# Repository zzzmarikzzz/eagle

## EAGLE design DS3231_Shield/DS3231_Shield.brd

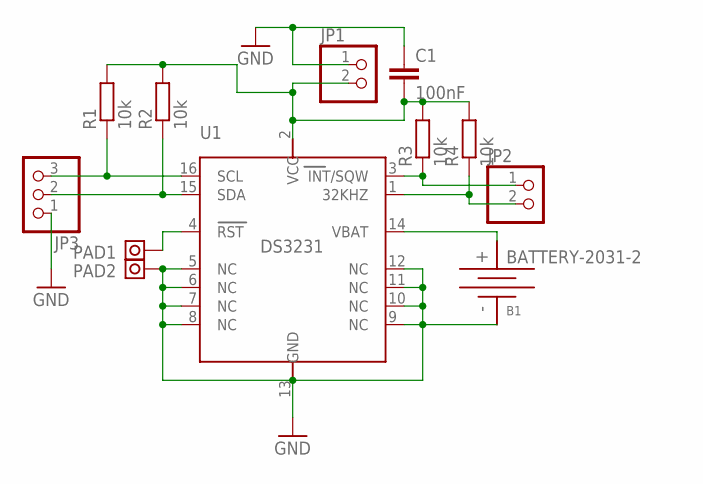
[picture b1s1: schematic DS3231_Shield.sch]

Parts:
B1: BATTERY-2031-2; BTH2032-2
C1: 100nF; C0805
JP1, JP2: PINHD-1X2; 1X02
JP3: PINHD-1X3; 1X03
PAD1, PAD2: PAD
R1, R2, R3, R4: 10k; R0805
U1: DS3231; SO16L

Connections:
GND: B1.-, C1.1, JP1.1, JP3.1, PAD2.P$1, U1.5 (NC), U1.6 (NC), U1.7 (NC), U1.8 (NC), U1.9 (NC), U1.10 (NC), U1.11 (NC), U1.12 (NC), U1.13 (GND)
unnamed: C1.2, JP1.2, R1.2, R2.2, R3.2, R4.2, U1.2 (VCC)
unnamed: B1.+, U1.14 (VBAT)
unnamed: PAD1.P$1, U1.4 (RST)
unnamed: JP3.2, R2.1, U1.15 (SDA)
unnamed: JP3.3, R1.1, U1.16 (SCL)
unnamed: JP2.1, R3.1, U1.3 (INT/SQW)
unnamed: JP2.2, R4.1, U1.1 (32KHZ)

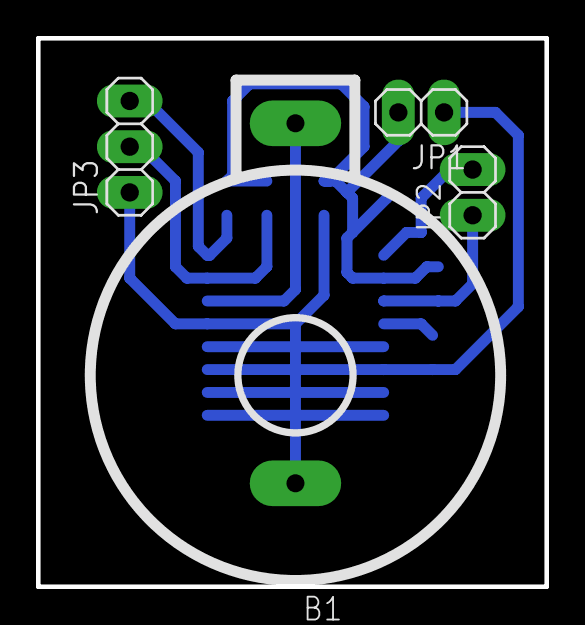
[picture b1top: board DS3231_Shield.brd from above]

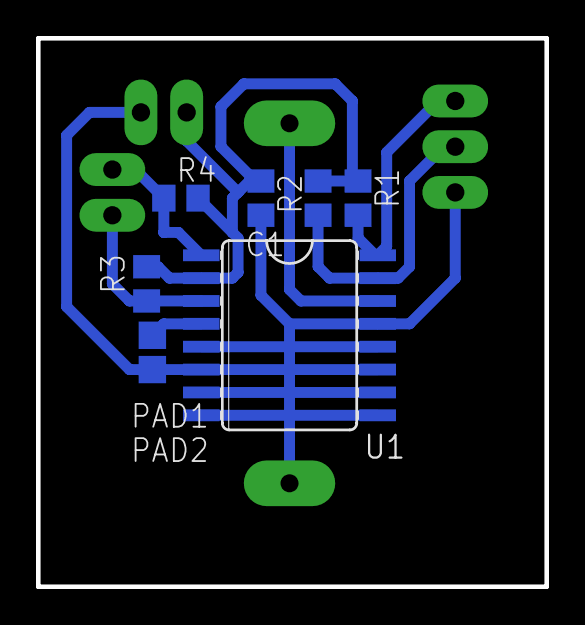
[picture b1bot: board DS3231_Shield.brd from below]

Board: 2 copper layers, 28.2 x 30.5 mm, 12 parts (8 on the bottom side), 8 nets.

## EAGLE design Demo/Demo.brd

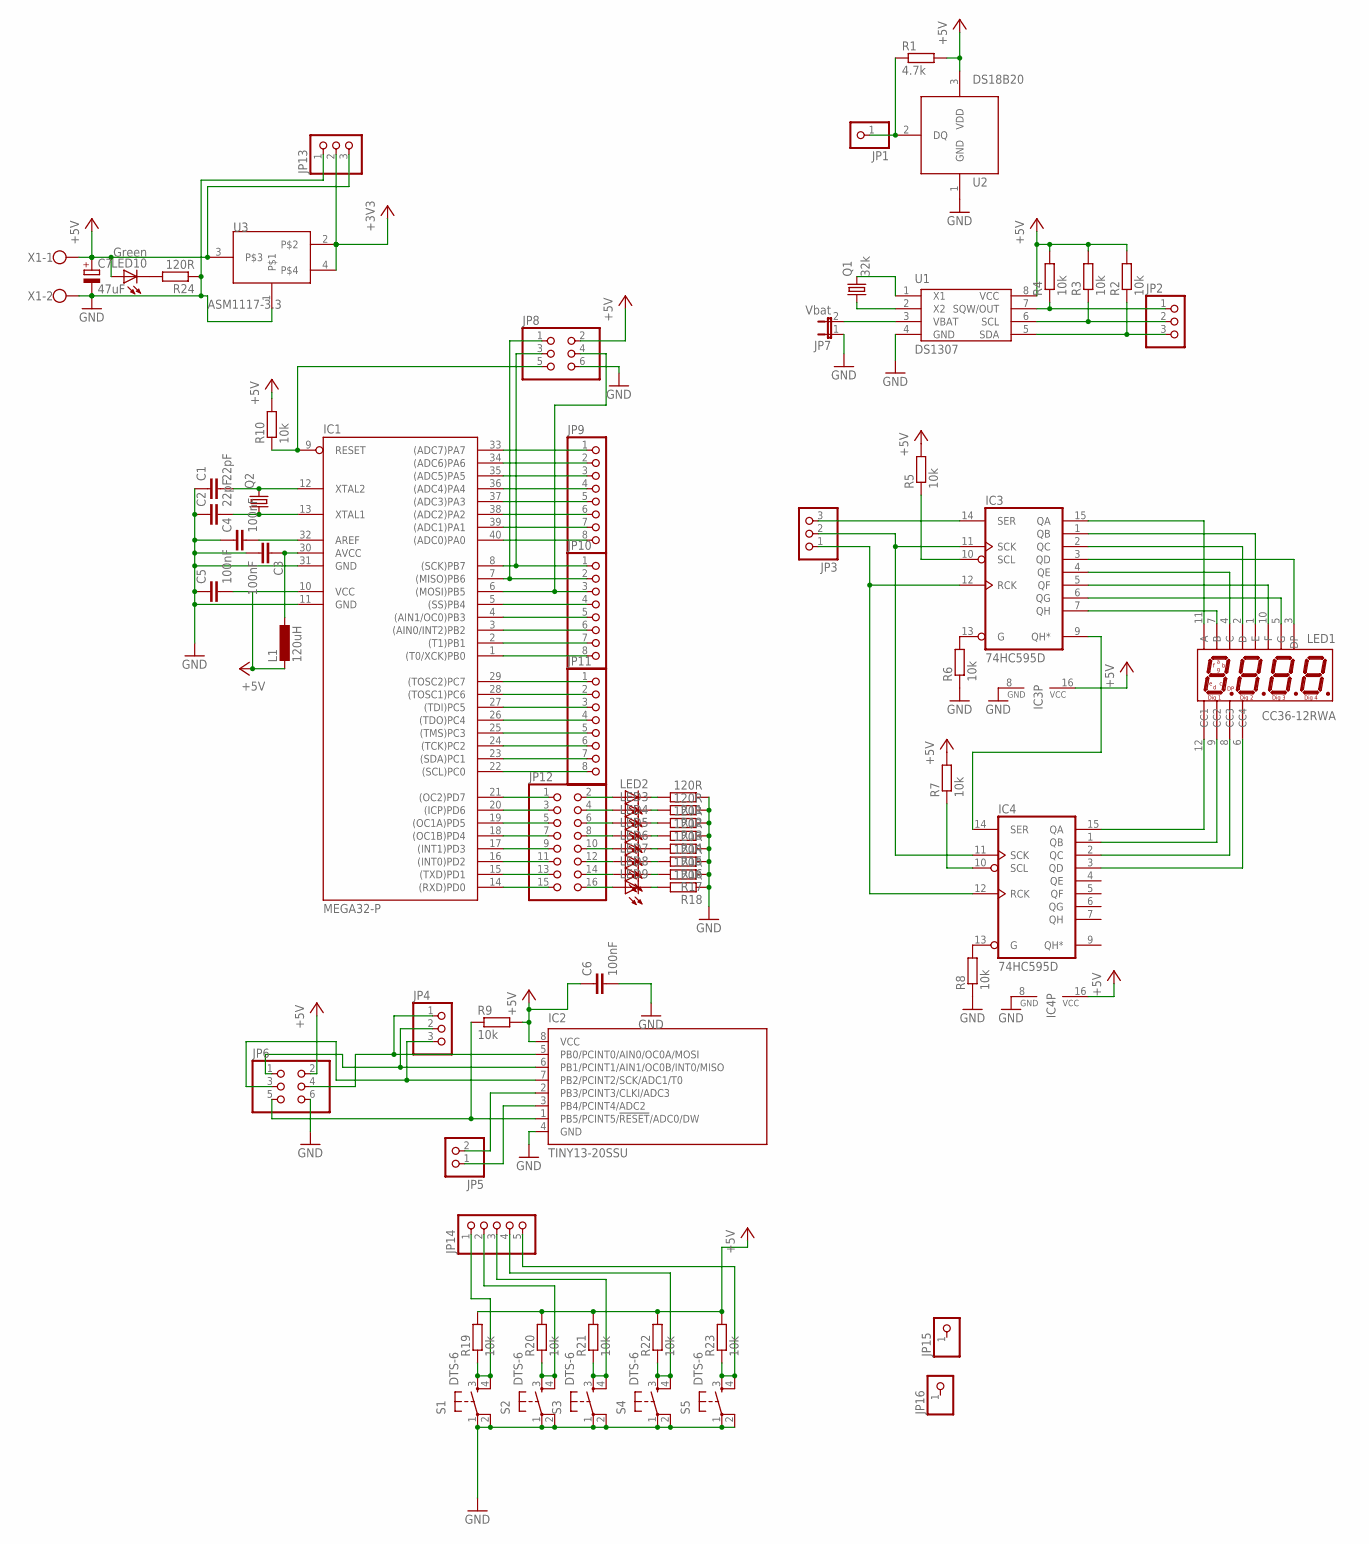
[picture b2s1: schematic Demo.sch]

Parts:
C1, C2: 22pF; C0805
C3, C4, C5, C6: 100nF; C0805
C7: 47uF; E2-5
IC1: MEGA32-P; DIL40
IC2: TINY13-20SSU; 8S1
IC3, IC4: 74HC595D; SO16
JP1, JP15, JP16: PINHD-1X1; 1X01
JP2, JP3, JP4, JP13: PINHD-1X3; 1X03
JP5: PINHD-1X2; 1X02
JP6, JP8: PINHD-2X3; 2X03
JP7: Vbat; JP1
JP9, JP10, JP11: PINHD-1X8; 1X08
JP12: PINHD-2X8; 2X08
JP14: PINHD-1X5; 1X05
L1: 120uH; 0204V
LED1: CC36-12RWA; 7SEG_4DIG
LED2, LED3, LED4, LED5, LED6, LED7, LED8, LED9: LEDSML0603; SML0603
LED10: Green; SML0603
Q1: 32k; TC38H
Q2: CRYSTALHC49S; HC49/S
R1: 4.7k; R0603
R2, R3, R4, R5, R6, R7, R8, R9, R10, R19, R20, R21, R22, R23: 10k; R0603
R11, R12, R13, R14, R15, R16, R17, R18, R24: 120R; R0603
S1, S2, S3, S4, S5: DTS-6
U1: DS1307; SOP08
U2: DS18B20; TO92
U3: ASM1117-3.3; SOT223
X1: W237-102

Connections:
+3V3: JP13.2, U3.2, U3.4
+5V: C5.2, C6.1, C7.+, IC1.10 (VCC), IC2.8 (VCC), IC3.16 (VCC), IC4.16 (VCC), JP6.2, JP8.2, JP13.3, L1.2, LED10.A, R1.2, R2.2, R3.2, R4.2, R5.2, R7.2, R9.2, R10.2, R19.2, R20.2, R21.2, R22.2, R23.2, U1.8 (VCC), U2.3 (VDD), U3.3, X1.1
GND: C1.1, C2.1, C3.2, C4.1, C5.1, C6.2, C7.-, IC1.11 (GND), IC1.31 (GND), IC2.4 (GND), IC3.8 (GND), IC4.8 (GND), JP6.6, JP7.1, JP8.6, JP13.1, R6.1, R8.1, R11.1, R12.1, R13.1, R14.1, R15.1, R16.1, R17.1, R18.1, R24.1, S1.1, S1.2, S2.1, S2.2, S3.1, S3.2, S4.1, S4.2, S5.1, S5.2, U1.4 (GND), U2.1 (GND), U3.1, X1.2
unnamed: JP1.1, R1.1, U2.2 (DQ)
unnamed: Q1.1, U1.2 (X2)
unnamed: Q1.2, U1.1 (X1)
unnamed: JP7.2, U1.3 (VBAT)
unnamed: JP2.3, R2.1, U1.5 (SDA)
unnamed: JP2.2, R3.1, U1.6 (SCL)
unnamed: JP2.1, R4.1, U1.7 (SQW/OUT)
unnamed: IC3.10 (SCL), R5.1
unnamed: IC3.13 (G), R6.2
unnamed: IC4.13 (G), R8.2
unnamed: IC4.10 (SCL), R7.1
unnamed: IC3.9 (QH*), IC4.14 (SER)
unnamed: IC3.15 (QA), LED1.11 (A)
unnamed: IC3.1 (QB), LED1.1 (E)
unnamed: IC3.2 (QC), LED1.2 (D)
unnamed: IC3.3 (QD), LED1.3 (DP)
unnamed: IC3.4 (QE), LED1.4 (C)
unnamed: IC3.5 (QF), LED1.10 (F)
unnamed: IC3.6 (QG), LED1.5 (G)
unnamed: IC3.7 (QH), LED1.7 (B)
unnamed: IC4.15 (QA), LED1.12 (CC1)
unnamed: IC4.1 (QB), LED1.9 (CC2)
unnamed: IC4.2 (QC), LED1.8 (CC3)
unnamed: IC4.3 (QD), LED1.6 (CC4)
unnamed: IC3.14 (SER), JP3.3
unnamed: IC3.11 (SCK), IC4.11 (SCK), JP3.2
unnamed: IC3.12 (RCK), IC4.12 (RCK), JP3.1
unnamed: IC2.1 (PB5/PCINT5/!RESET!/ADC0/DW), JP6.5, R9.1
unnamed: C1.2, IC1.12 (XTAL2), Q2.2
unnamed: IC2.6 (PB1/PCINT1/AIN1/OC0B/INT0/MISO), JP4.2, JP6.1
unnamed: IC2.7 (PB2/PCINT2/SCK/ADC1/T0), JP4.3, JP6.3
unnamed: IC2.5 (PB0/PCINT0/AIN0/OC0A/MOSI), JP4.1, JP6.4
unnamed: IC2.3 (PB4/PCINT4/ADC2), JP5.1
unnamed: IC2.2 (PB3/PCINT3/CLKI/ADC3), JP5.2
unnamed: C2.2, IC1.13 (XTAL1), Q2.1
unnamed: C4.2, IC1.32 (AREF)
unnamed: LED10.C, R24.2
unnamed: C3.1, IC1.30 (AVCC), L1.1
unnamed: IC1.9 (RESET), JP8.5, R10.1
unnamed: IC1.33 ((ADC7)PA7), JP9.1
unnamed: IC1.34 ((ADC6)PA6), JP9.2
unnamed: IC1.35 ((ADC5)PA5), JP9.3
unnamed: IC1.36 ((ADC4)PA4), JP9.4
unnamed: IC1.37 ((ADC3)PA3), JP9.5
unnamed: IC1.38 ((ADC2)PA2), JP9.6
unnamed: IC1.39 ((ADC1)PA1), JP9.7
unnamed: IC1.40 ((ADC0)PA0), JP9.8
unnamed: IC1.8 ((SCK)PB7), JP8.3, JP10.1
unnamed: IC1.7 ((MISO)PB6), JP8.1, JP10.2
unnamed: IC1.6 ((MOSI)PB5), JP8.4, JP10.3
unnamed: IC1.5 ((SS)PB4), JP10.4
unnamed: IC1.4 ((AIN1/OC0)PB3), JP10.5
unnamed: IC1.3 ((AIN0/INT2)PB2), JP10.6
unnamed: IC1.2 ((T1)PB1), JP10.7
unnamed: IC1.1 ((T0/XCK)PB0), JP10.8
unnamed: IC1.29 ((TOSC2)PC7), JP11.1
unnamed: IC1.28 ((TOSC1)PC6), JP11.2
unnamed: IC1.27 ((TDI)PC5), JP11.3
unnamed: IC1.26 ((TDO)PC4), JP11.4
unnamed: IC1.25 ((TMS)PC3), JP11.5
unnamed: IC1.24 ((TCK)PC2), JP11.6
unnamed: IC1.23 ((SDA)PC1), JP11.7
unnamed: IC1.22 ((SCL)PC0), JP11.8
unnamed: IC1.21 ((OC2)PD7), JP12.1
unnamed: IC1.20 ((ICP)PD6), JP12.3
unnamed: IC1.19 ((OC1A)PD5), JP12.5
unnamed: IC1.18 ((OC1B)PD4), JP12.7
unnamed: IC1.17 ((INT1)PD3), JP12.9
unnamed: IC1.16 ((INT0)PD2), JP12.11
unnamed: IC1.15 ((TXD)PD1), JP12.13
unnamed: IC1.14 ((RXD)PD0), JP12.15
unnamed: JP12.2, LED2.A
unnamed: JP12.4, LED3.A
unnamed: JP12.6, LED4.A
unnamed: JP12.8, LED5.A
unnamed: JP12.10, LED6.A
unnamed: JP12.12, LED7.A
unnamed: JP12.14, LED8.A
unnamed: JP12.16, LED9.A
unnamed: LED2.C, R11.2
unnamed: LED3.C, R12.2
unnamed: LED4.C, R13.2
unnamed: LED5.C, R14.2
unnamed: LED6.C, R15.2
unnamed: LED7.C, R16.2
unnamed: LED8.C, R17.2
unnamed: LED9.C, R18.2
unnamed: JP14.1, R19.1, S1.3, S1.4
unnamed: JP14.2, R20.1, S2.3, S2.4
unnamed: JP14.3, R21.1, S3.3, S3.4
unnamed: JP14.4, R22.1, S4.3, S4.4
unnamed: JP14.5, R23.1, S5.3, S5.4

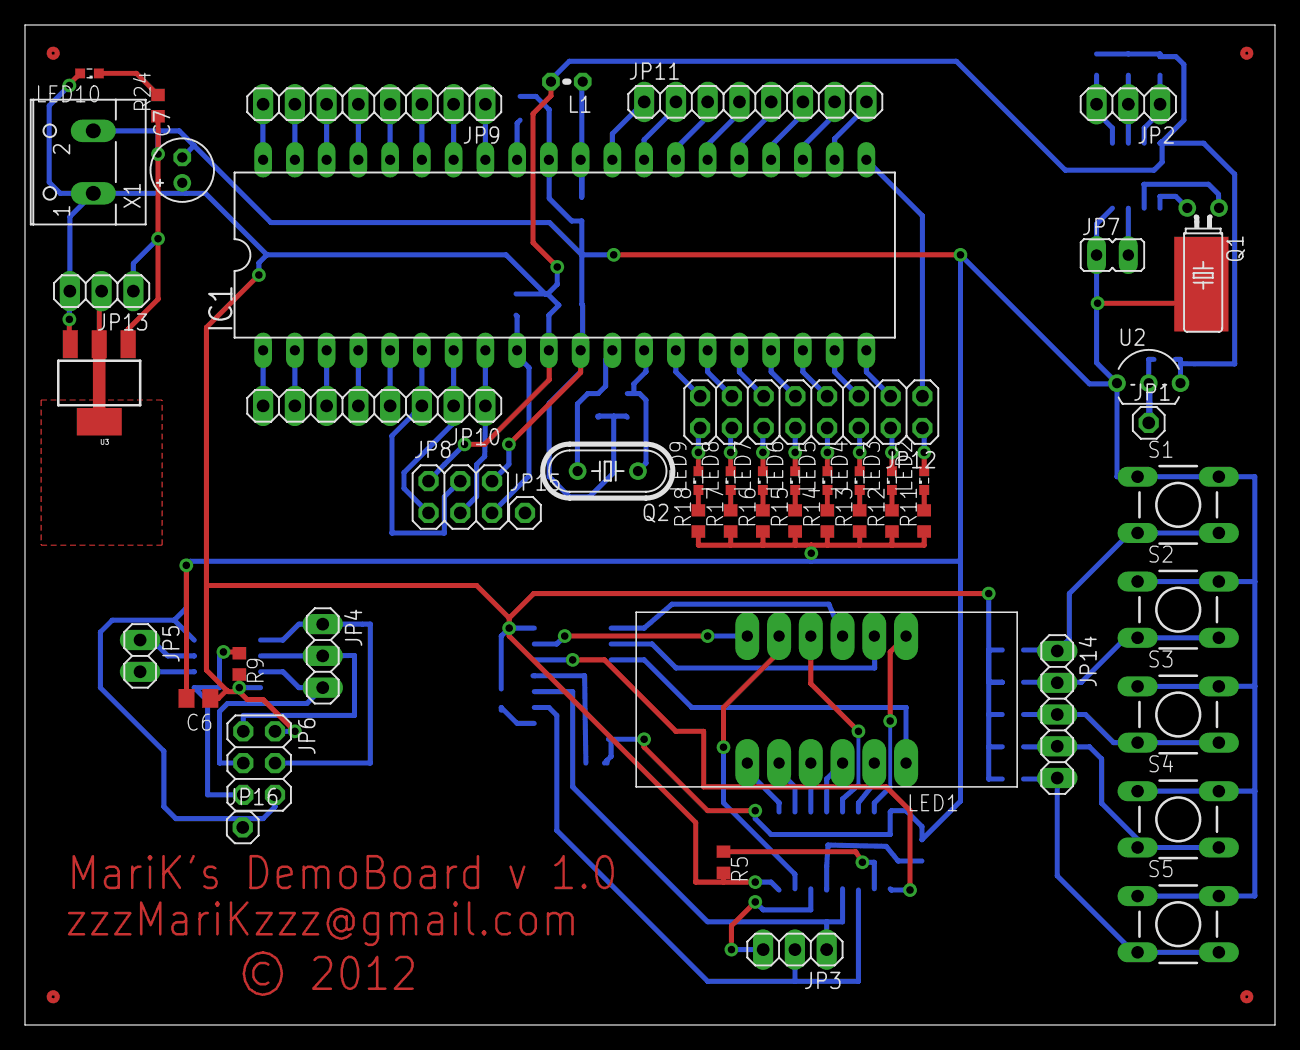
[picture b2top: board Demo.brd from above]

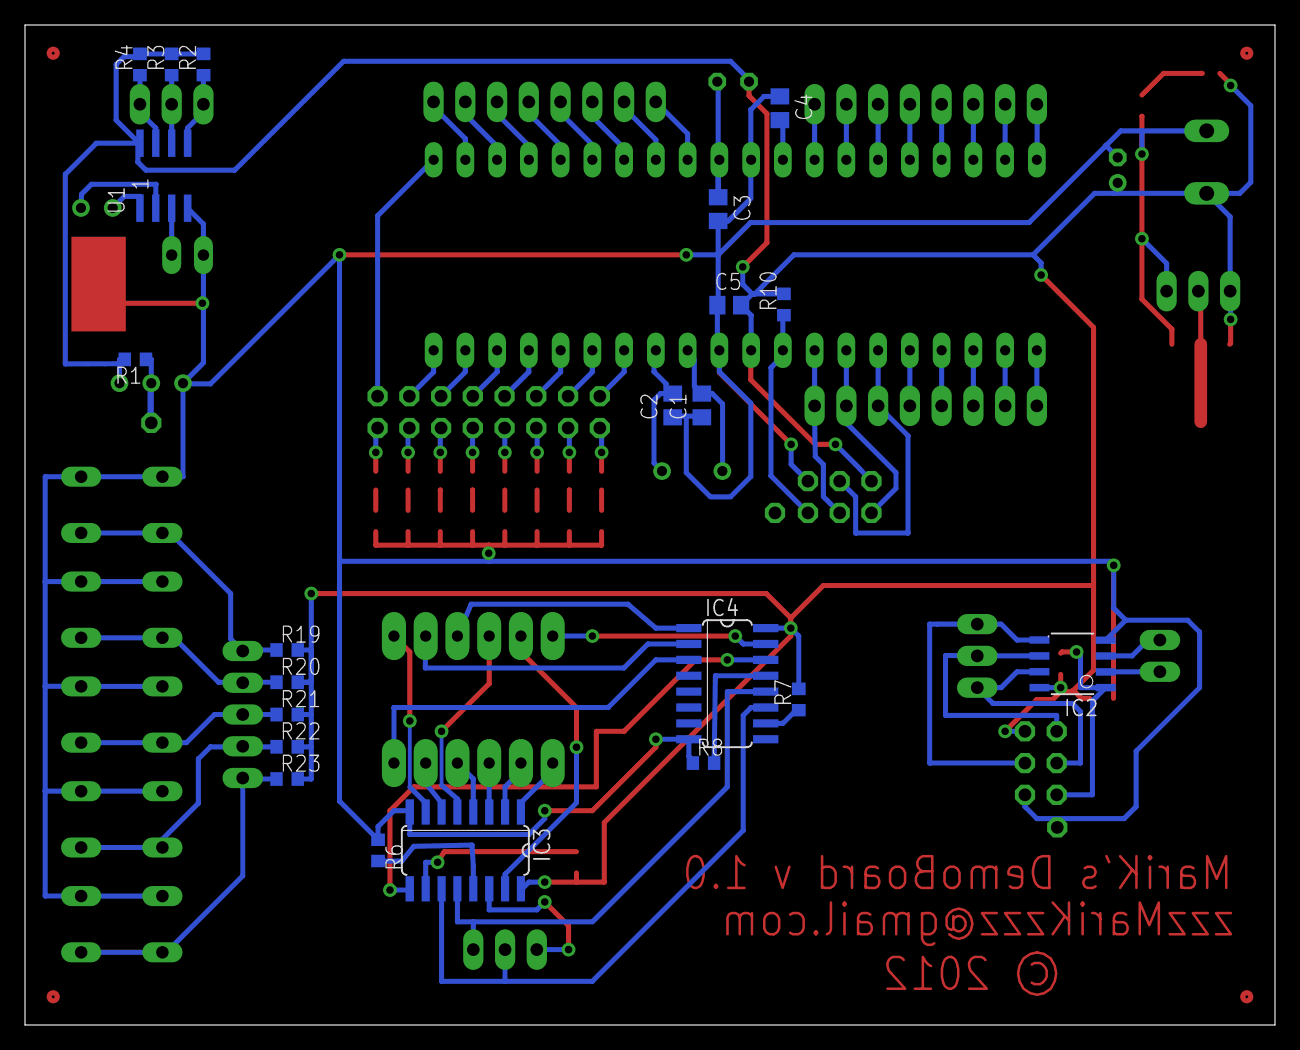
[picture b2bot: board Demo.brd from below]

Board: 2 copper layers, 100.0 x 80.0 mm, 73 parts (22 on the bottom side), 95 nets.

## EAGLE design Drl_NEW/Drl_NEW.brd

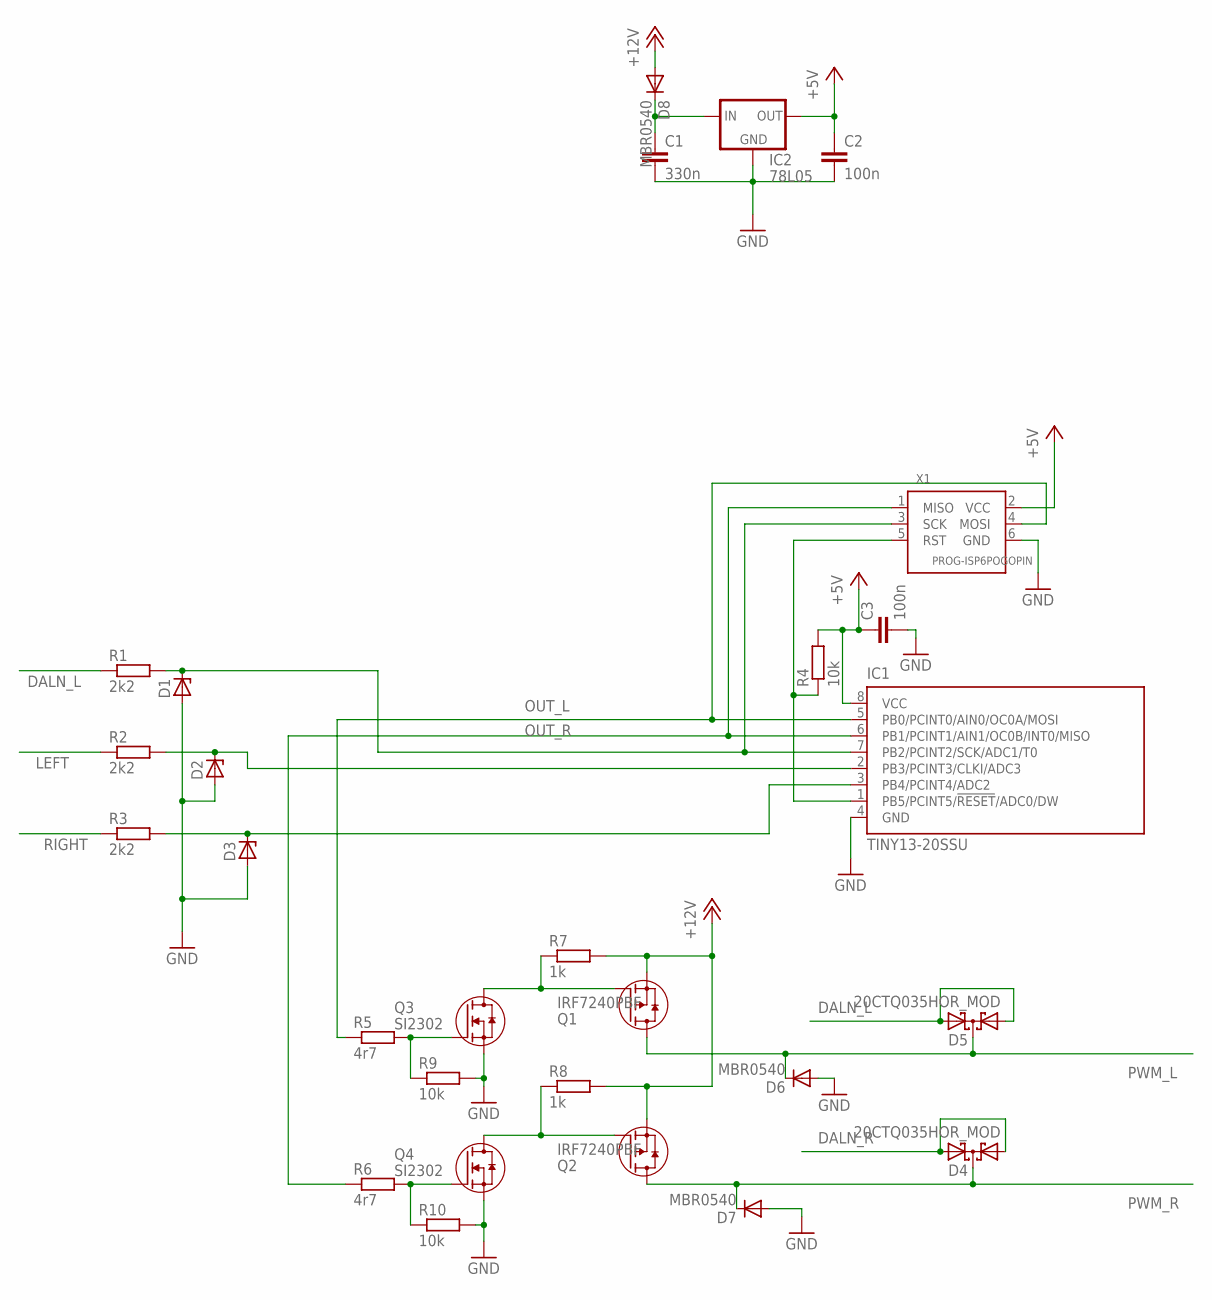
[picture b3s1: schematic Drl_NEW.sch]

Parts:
C1: 330n; C0805
C2, C3: 100n; C0805
D1, D2, D3: ZENER-DIODESOD80C; SOD80C
D4, D5: 20CTQ035HOR_MOD; TO220AB_MOD
D6, D7, D8: MBR0540; SOD-123_MINI-SMA
IC1: TINY13-20SSU; 8S1
IC2: 78L05; 78LXX-SOT89
Q1, Q2: IRF7240PBF; SO08
Q3, Q4: SI2302; SOT-23-GSD
R1, R2, R3: 2k2; R0603
R4, R9, R10: 10k; R0603
R5, R6: 4r7; R0603
R7, R8: 1k; R0603
X1: PROG-ISP6POGOPIN; PROG_POGOPIN

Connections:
+5V: C2.1, C3.1, IC1.8 (VCC), IC2.OUT, R4.2, X1.2 (VCC)
+12V: D8.A, Q1.1 (S), Q1.2 (S), Q1.3 (S), Q2.1 (S), Q2.2 (S), Q2.3 (S), R7.2, R8.2
DALN_L: D5.A1, D5.A2, R1.1
DALN_R: D4.A1, D4.A2
GND: C1.2, C2.2, C3.2, D1.A, D2.A, D3.A, D6.A, D7.A, IC1.4 (GND), IC2.GND@0 (GND), IC2.GND@1 (GND), Q3.S, Q4.S, R9.2, R10.2, X1.6 (GND)
LEFT: R2.1
unnamed: D2.C, IC1.2 (PB3/PCINT3/CLKI/ADC3), R2.2
unnamed: IC1.1 (PB5/PCINT5/!RESET!/ADC0/DW), R4.1, X1.5 (RST)
unnamed: Q2.4 (G), Q4.D, R8.1
unnamed: C1.1, D8.C, IC2.IN
unnamed: D3.C, IC1.3 (PB4/PCINT4/ADC2), R3.2
unnamed: Q1.4 (G), Q3.D, R7.1
unnamed: Q3.G, R5.2, R9.1
unnamed: Q4.G, R6.2, R10.1
unnamed: D1.C, IC1.7 (PB2/PCINT2/SCK/ADC1/T0), R1.2, X1.3 (SCK)
OUT_L: IC1.5 (PB0/PCINT0/AIN0/OC0A/MOSI), R5.1, X1.4 (MOSI)
OUT_R: IC1.6 (PB1/PCINT1/AIN1/OC0B/INT0/MISO), R6.1, X1.1 (MISO)
PWM_L: D5.C, D6.C, Q1.5 (D), Q1.6 (D), Q1.7 (D), Q1.8 (D)
PWM_R: D4.C, D7.C, Q2.5 (D), Q2.6 (D), Q2.7 (D), Q2.8 (D)
RIGHT: R3.1

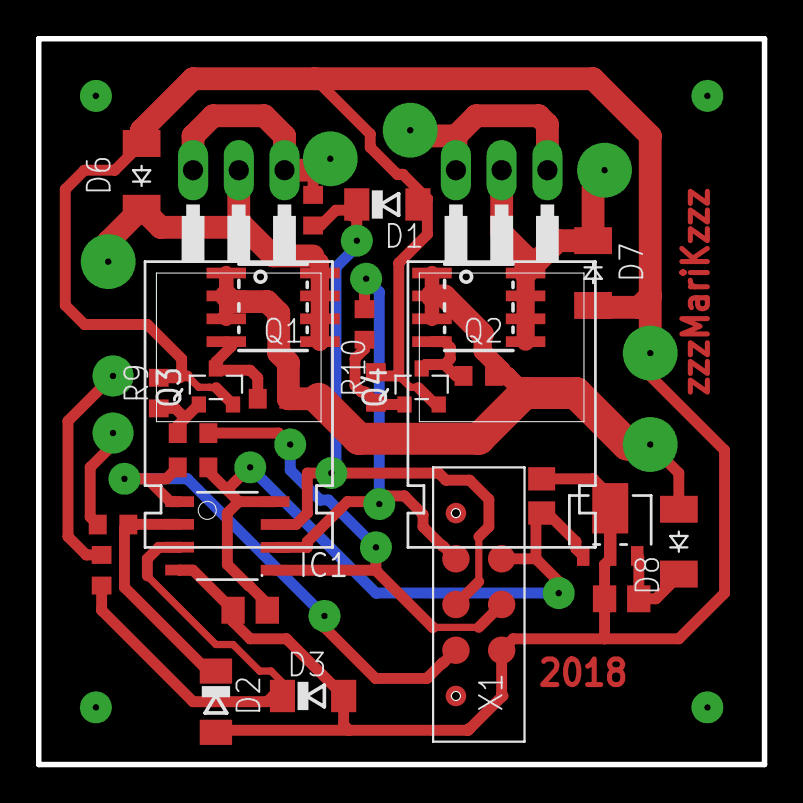
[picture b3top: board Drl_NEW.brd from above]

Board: 2 copper layers, 40.3 x 40.3 mm, 28 parts (0 on the bottom side), 18 nets.

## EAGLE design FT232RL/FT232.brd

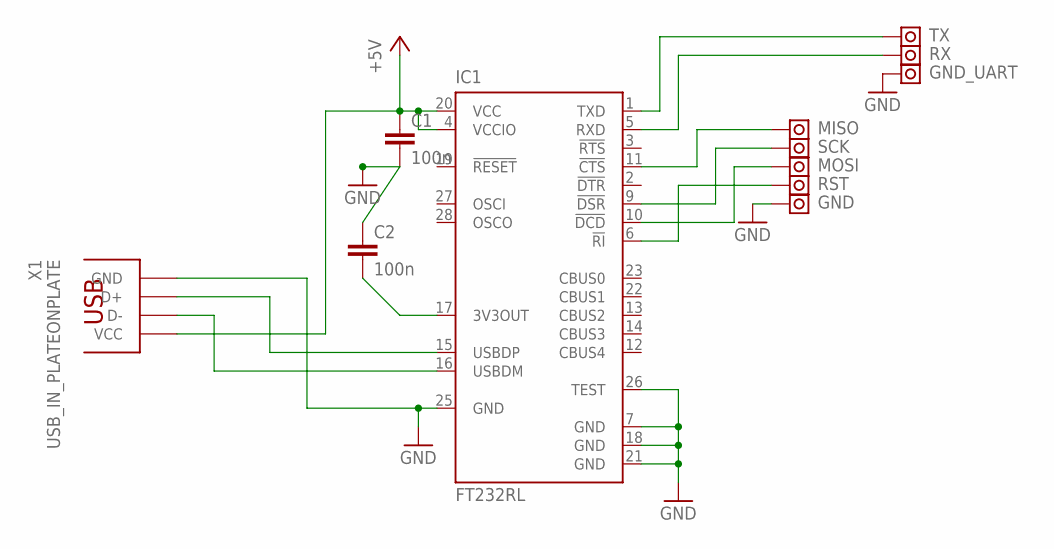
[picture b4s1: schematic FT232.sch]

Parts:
C1: 100n; C0805
C2: 100n; 0805
GND: PAD
GND_UART: PAD
IC1: FT232RL; SSOP28
MISO: PAD
MOSI: PAD
RST: PAD
RX: PAD
SCK: PAD
TX: PAD
X1: USB_IN_PLATEONPLATE; USB_IN_PLATE

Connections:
+5V: C1.1, IC1.4 (VCCIO), IC1.20 (VCC), X1.VCC
GND: C1.2, C2.1, GND.P$1, GND_UART.P$1, IC1.7 (GND), IC1.18 (GND), IC1.21 (GND), IC1.25 (GND), IC1.26 (TEST), X1.GND
unnamed: IC1.1 (TXD), TX.P$1
unnamed: IC1.15 (USBDP), X1.D+
unnamed: IC1.16 (USBDM), X1.D-
unnamed: C2.2, IC1.17 (3V3OUT)
unnamed: IC1.5 (RXD), RX.P$1
unnamed: IC1.11 (!CTS), MISO.P$1
unnamed: IC1.9 (!DSR), SCK.P$1
unnamed: IC1.10 (!DCD), MOSI.P$1
unnamed: IC1.6 (!RI), RST.P$1

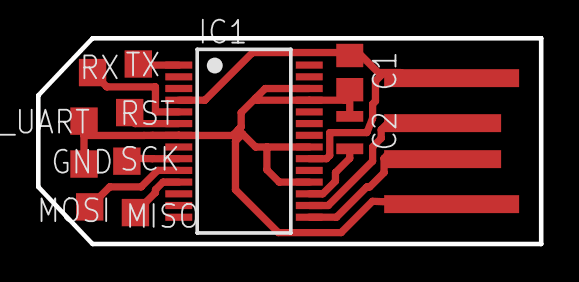
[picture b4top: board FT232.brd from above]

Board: 2 copper layers, 27.9 x 11.4 mm, 12 parts (0 on the bottom side), 11 nets.

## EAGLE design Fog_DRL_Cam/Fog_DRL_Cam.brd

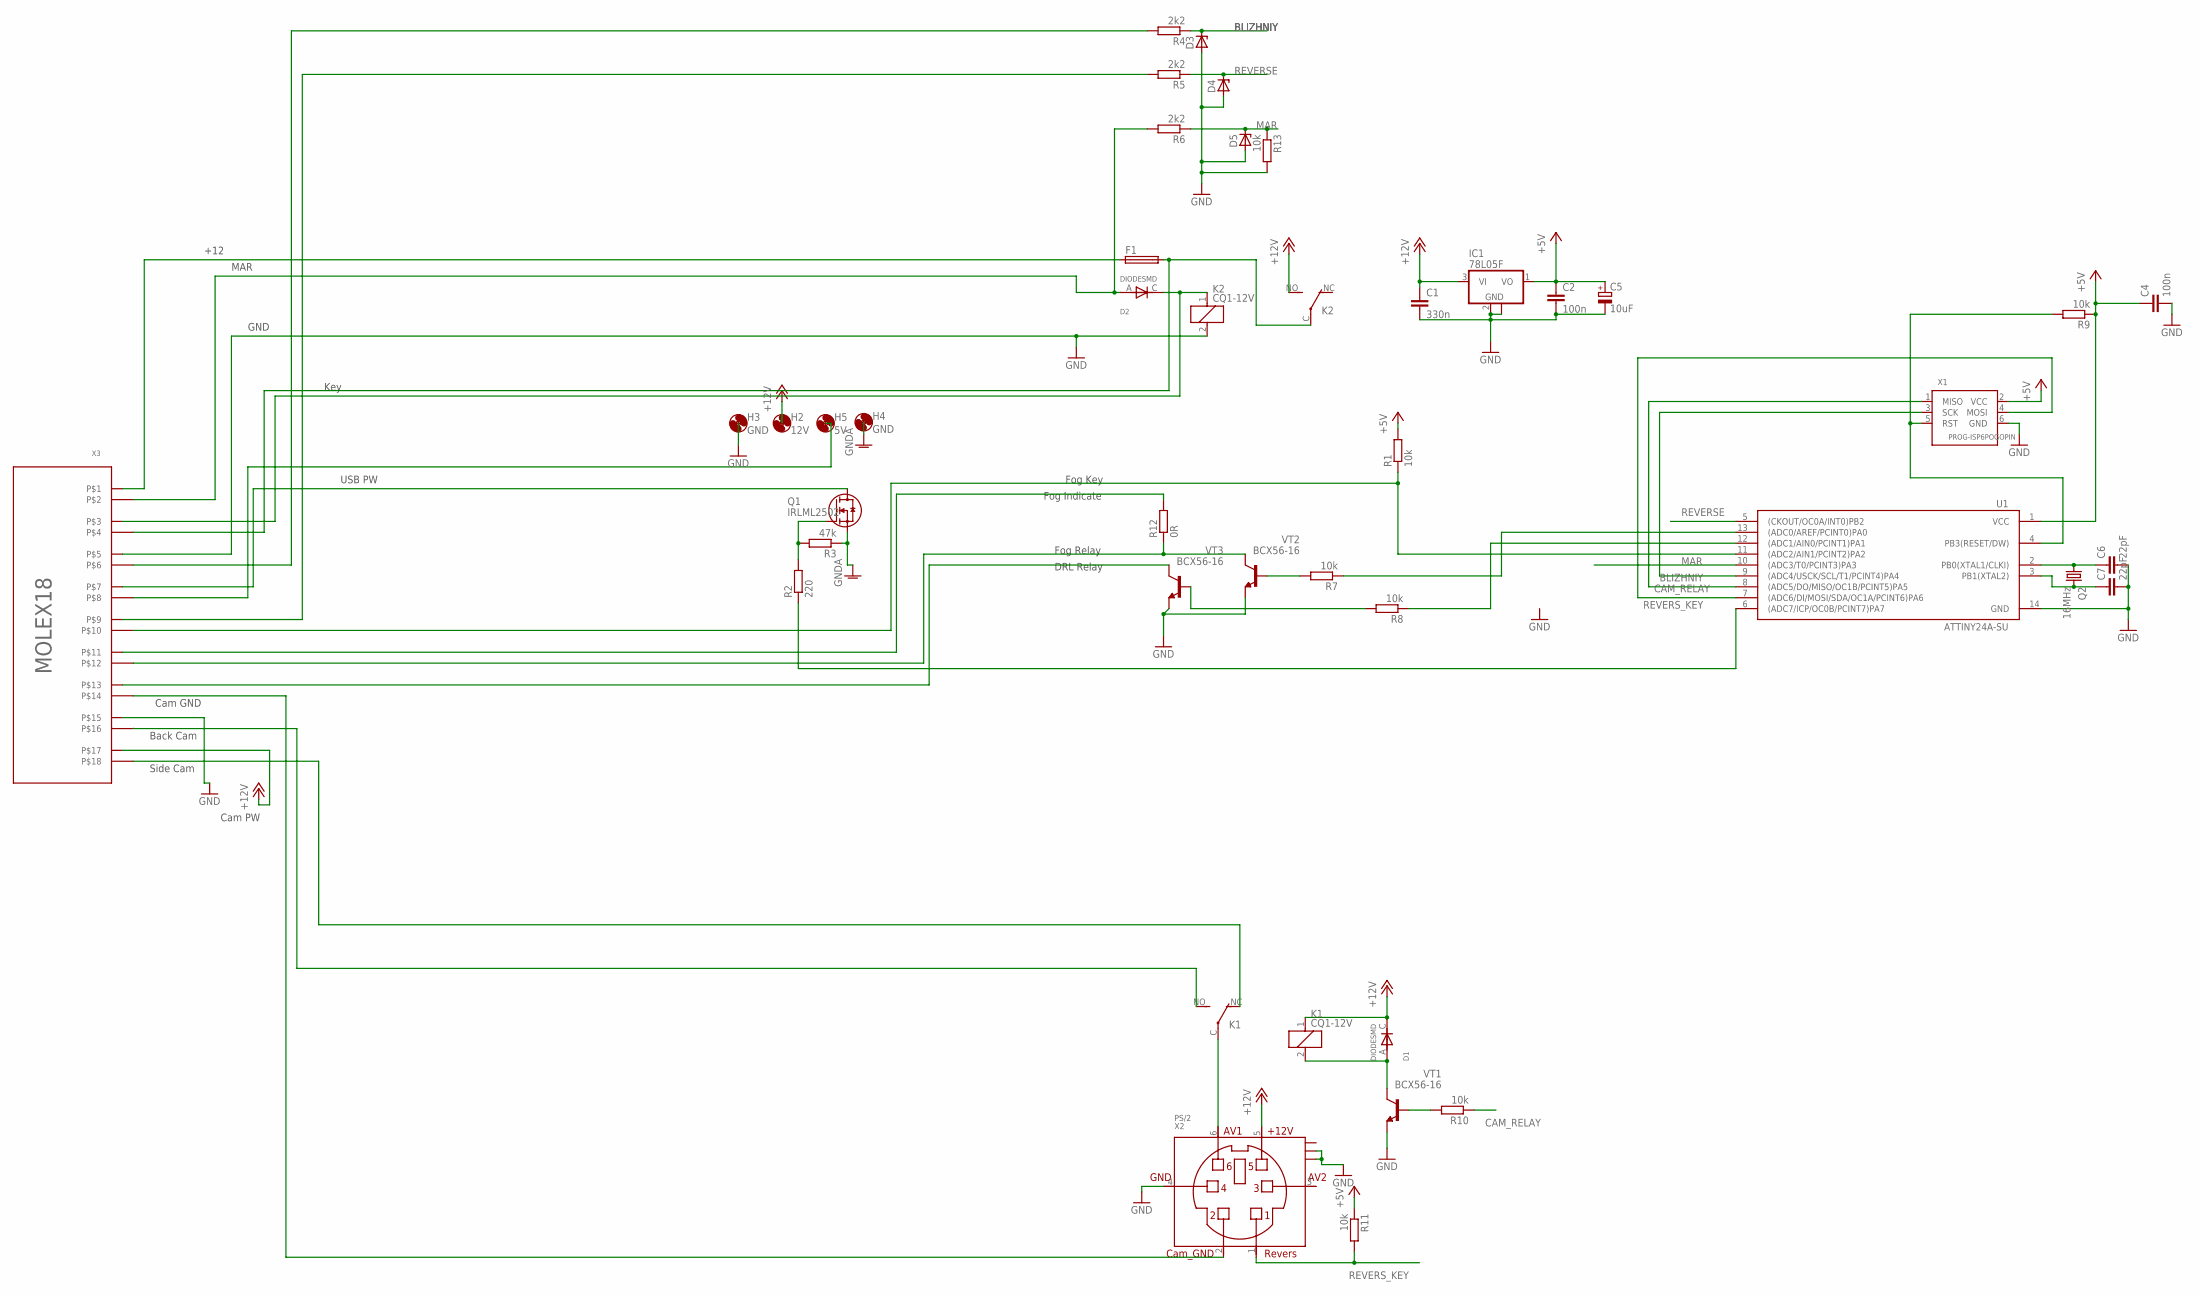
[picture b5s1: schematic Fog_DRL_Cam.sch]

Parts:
C1: 330n; C0805
C2, C4: 100n; C0603
C5: 10uF; CT3216
C6, C7: 22pF; C0603
D1, D2: DIODESMD; DO214AC
D3, D4, D5: ZENER-DIODESOD80C; SOD80C
F1: SH22,5A
H2: 12V; 3,0
H3, H4: GND; 3,0
H5: 5V; 3,0
IC1: 78L05F; SOT89
K1, K2: CQ1-12V; CQ1
Q1: IRLML2502; SOT-23-GSD
Q2: 16MHz; HC49/S
R1, R7, R8, R9, R10, R11, R13: 10k; R0603
R2: 220; R0603
R3: 47k; R0603
R4, R5, R6: 2k2; R0603
R12: 0R; R0603
U1: ATTINY24A-SU; SO14
VT1, VT2, VT3: BCX56-16; SOT89-BCE
X1: PROG-ISP6POGOPIN; PROG_POGOPIN
X2: PS/2
X3: MOLEX18

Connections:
+5V: C2.1, C4.1, C5.+, IC1.1 (VO), R1.2, R9.1, R11.1, U1.1 (VCC), X1.2 (VCC)
+12V: C1.1, D1.C (KATOD), H2.P$1, IC1.3 (VI), K1.1, K2.NO (S), X2.5, X3.P$17
BLIZHNIY: D3.C, R4.1, U1.9 ((ADC4/USCK/SCL/T1/PCINT4)PA4), X1.3 (SCK)
CAM_RELAY: R10.1, U1.8 ((ADC5/DO/MISO/OC1B/PCINT5)PA5), X1.1 (MISO)
GND: C1.2, C2.2, C4.2, C5.-, C6.2, C7.2, D3.A, D4.A, D5.A, H3.P$1, IC1.2 (GND), IC1.2@1 (GND), K2.2, R13.2, U1.14 (GND), VT1.E, VT2.E, VT3.E, X1.6 (GND), X2.4, X2.GND0, X2.GND2, X3.P$5, X3.P$15
GNDA: H4.P$1, Q1.S, R3.1
MAR: D5.C, R6.1, R13.1, U1.10 ((ADC3/T0/PCINT3)PA3)
unnamed: K1.NO (S), X3.P$16
unnamed: R12.2, X3.P$11
unnamed: X2.2, X3.P$14
unnamed: K1.C, X2.6
unnamed: D1.A (ANOD), K1.2, VT1.C, VT1.C@1 (C)
unnamed: F1.1, X3.P$1
unnamed: H5.P$1, X3.P$8
unnamed: Q1.D, X3.P$7
unnamed: F1.2, K2.C, X3.P$4
unnamed: D2.C (KATOD), K2.1, X3.P$3
unnamed: D2.A (ANOD), R6.2, X3.P$2
unnamed: R2.1, U1.6 ((ADC7/ICP/OC0B/PCINT7)PA7)
unnamed: VT3.C, VT3.C@1 (C), X3.P$13
unnamed: R12.1, VT2.C, VT2.C@1 (C), X3.P$12
unnamed: R8.1, U1.12 ((ADC1/AIN0/PCINT1)PA1)
unnamed: R7.1, U1.13 ((ADC0/AREF/PCINT0)PA0)
unnamed: R1.1, U1.11 ((ADC2/AIN1/PCINT2)PA2), X3.P$10
unnamed: Q1.G, R2.2, R3.2
unnamed: R5.2, X3.P$9
unnamed: R4.2, X3.P$6
unnamed: R7.2, VT2.B
unnamed: R8.2, VT3.B
unnamed: C6.1, Q2.1, U1.2 (PB0(XTAL1/CLKI))
unnamed: R10.2, VT1.B
unnamed: K1.NC (O), X3.P$18
unnamed: R9.2, U1.4 (PB3(RESET/DW)), X1.5 (RST)
unnamed: C7.1, Q2.2, U1.3 (PB1(XTAL2))
REVERSE: D4.C, R5.1, U1.5 ((CKOUT/OC0A/INT0)PB2)
REVERS_KEY: R11.2, U1.7 ((ADC6/DI/MOSI/SDA/OC1A/PCINT6)PA6), X1.4 (MOSI), X2.1

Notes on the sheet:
Fog Relay
DRL Relay
Fog Key
Fog Indicate
USB PW
+12
MAR
GND
Cam PW
Key
Back Cam
Side Cam
Cam GND

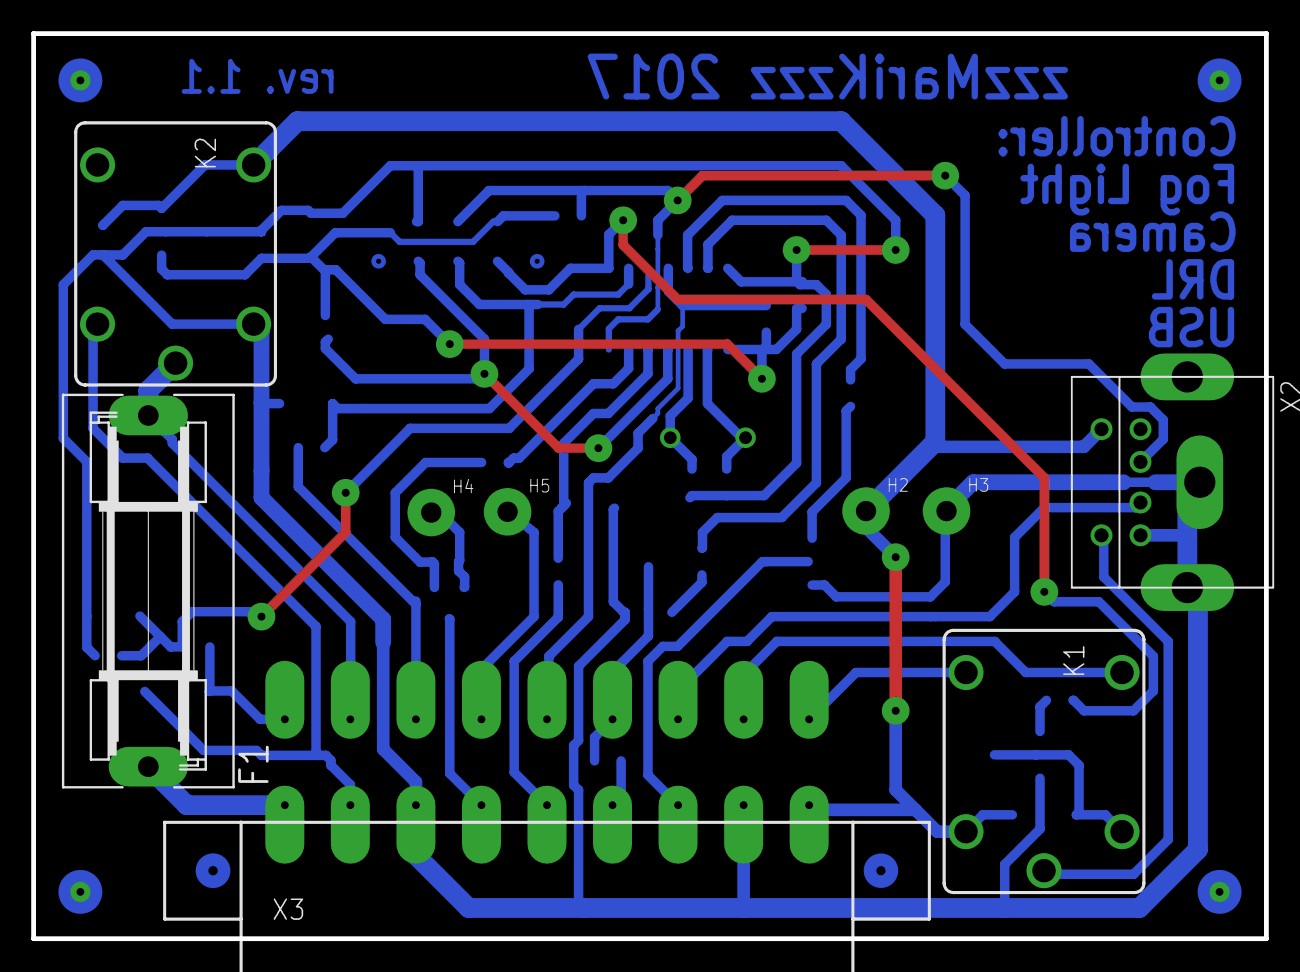
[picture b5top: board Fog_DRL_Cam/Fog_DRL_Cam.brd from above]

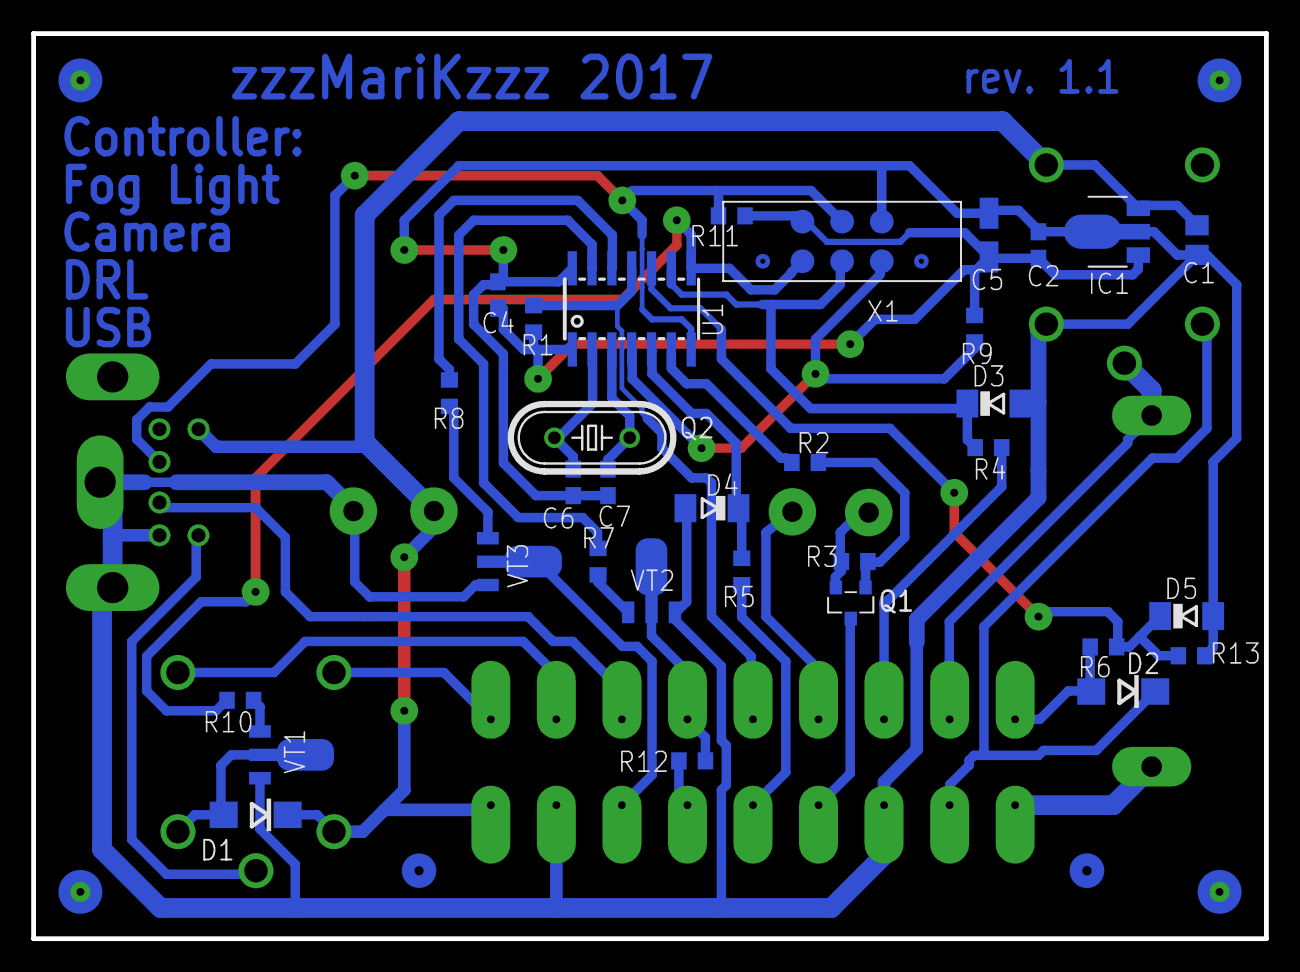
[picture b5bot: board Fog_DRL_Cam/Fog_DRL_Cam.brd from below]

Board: 2 copper layers, 79.0 x 58.0 mm, 41 parts (32 on the bottom side), 36 nets.

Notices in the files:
Demo/Demo.brd:
© 2012
